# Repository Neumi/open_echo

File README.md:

---
layout: home
title: Open Echo
nav_exclude: true
---

<div align="center">
  
</div>

## Universal Open-Source SONAR Controller and Development Stack

An ongoing open-source hardware and software project for building sonar systems for testing, boating, bathymetry, and research.

[Discord](https://discord.com/invite/rerCyqAcrw) | [Getting Started Guide](documentation/getting_started/index.md) | [Hardware Files](https://github.com/neumi/open_echo/tree/main/TUSS4470_shield_002/TUSS4470_shield_hardware/TUSS4470_shield)

## Overview

Open Echo makes SONAR technology accessible for developers, researchers, and hobbyists. It supports a wide variety of commercial and DIY ultrasonic transducers in both water and air, covering frequencies from 40 kHz up to 1000 kHz.

Use cases range from reverse-engineering car parking sensors and reading depth data on a yacht, to operating a Lowrance Tripleshot side-scan transducer or streaming data to a Pixhawk on a custom boat.

### Key Features

* **Universal Transducer Support:** Works with commercial and DIY transducers in water and air.
* **Flexible Firmware:** Run the [RAW Data Firmware](documentation/getting_started/TUSS4470_firmware.md) to process echoes yourself, or the [NMEA Output Firmware](https://github.com/neumi/open_echo/tree/main/TUSS4470_shield_002/arduino/NMEA_DBT_OUT/NMEA_DBT_OUT.ino) for NMEA0183 DBT compatibility (sends depth data directly to PCs, Pixhawk, or marine controllers).
* **Python Interface:** The [desktop software](documentation/getting_started/desktop_interface.md) provides live raw data visualization and TCP data streaming.
* **Tested Range:** Confirmed depth tracking of >50 m in water.
* **Network Ready:** Includes a PicoW implementation (software only, the shield itself is Arduino UNO R3 compatible) that transfers RAW data over UDP directly to the Python interface.

## Hardware & Getting Started

The primary development platform is the [TUSS4470 Arduino Shield](documentation/getting_started/TUSS4470_hardware.md). It stacks directly on top of an Arduino Uno to drive the TUSS4470 ultrasonic driver.

**Upcoming Board:** A new development version is in the works and will hopefully be released in the coming weeks. It features an on-board boost converter and slightly improved signal routing.

* **Powering (Current Board):** Provide driver voltage via Arduino VIN or the external XT30 connector. You can also currently use an MT3608 boost converter to step up USB power to your required drive voltage (requires manual soldering until the new board is released).
* **Capabilities:** Drives transducers from 40–1000 kHz, filters signals, and sends raw echo data to the backend. It captures 1800 samples at 13.2 µs/sample (roughly an 18m range in water at 8-bit resolution). You can manually add delays in the code to extend the detection range for further distances.

### Getting the Hardware

1. **Elecrow (Pre-Built):** Buy a fully assembled and tested board here: [Elecrow Open Echo TUSS4470](https://www.elecrow.com/open-echo-tuss4470-development-shield.html)
2. **Build Your Own:** Order the [Hardware Files](https://github.com/neumi/open_echo/tree/main/TUSS4470_shield_002/TUSS4470_shield_hardware/TUSS4470_shield) from your preferred PCB manufacturer (JLCPCB recommended).
3. **Directly from me (Germany/EU):** If Elecrow is out of stock or you want to reduce shipping costs within Germany, email me at: `openechoes@gmail.com`.

> **Note:** All profits go directly toward supporting the project. Please understand that I can only provide support if you order the boards directly from me or Elecrow.

## Open Echo Interface Software

The [Python Interface Software](documentation/getting_started/desktop_interface.md) connects to boards running the RAW Data Firmware. It serves as a simple backend to view live echograms and output TCP depth data streams. (Configuration tweaking directly from the UI will be added later).

Live echogram in water (6x speed):  

*(Static raw data waterfall chart available [here](documentation/images/echo_software_screenshot.jpg))*

## Test Results: Baltic Sea

Tested using a built-in 150 kHz SEAFARER transducer, powered at 15-20 V via an MT3608 boost converter from USB. Data capture in the plots begins at the bottom.

<table>
  <tr>
    <td align="center">
      <br/>
      <sub><b>38 m range test</b></sub>
    </td>
    <td align="center">
      <br/>
      <sub><b>Kiel Channel sand and mud</b></sub>
    </td>
    <td align="center">
      <br/>
      <sub><b>Slope near Stollergrund</b></sub>
    </td>
  </tr>
  <tr>
    <td align="center">
      <br/>
      <sub><b>Stones and sandy seabed</b></sub>
    </td>
    <td align="center">
      <br/>
      <sub><b>Fish detection</b></sub>
    </td>
    <td align="center">
      <br/>
      <sub><b>Multiple reflections and seaweed</b></sub>
    </td>
  </tr>
</table>

## Transducers

Open Echo has been tested with multiple transducers. Here is a curated list of tested hardware:

| Transducer Name | Rating | Description | Freq. | Range Air/Water | Price | Link |
| --- | --- | --- | --- | --- | --- | --- |
| NASA / Seafarer 150kHz | ⭐⭐⭐ | NASA in-hull boat transducer for echo sounding / fish-finding | 150kHz | >2m / >50m | 50-100€ | [Link](https://www.nasamarine.com/product/depth-transducer-with-7-metre-cable/7) |
| Raymarine CPT-S | ⭐⭐⭐ | High-quality in-hull transducer with two frequencies | 50/200kHz | 2m / >50m | 200€ | [Link](https://www.raymarine.com/de-de/unsere-produkte/fischfinder-und-sonarmodule/fischfindergeber/cpt-s-durchbruchgeber) |
| Lowrance Tripleshot | ⭐⭐⭐ | Sidescan transducer (three FANS + temp + down-scan) | 200/455/600kHz | 0m / >20m | 200€ | [Link](https://www.echolotzentrum.de/shop/lowrance-tripleshot-heckgeber/) |
| Cheap Bathymetry | ⭐⭐⭐ | Good range and price/performance (can be hard to order) | 200kHz | 2m / >30m | 25€ | [Link](https://www.alibaba.com/product-detail/Range-customization-lakes-river-surveys-no_1600829423846.html) |
| Car Parking Sensor | ⭐⭐ | Great for air, works in water (not recommended for marine) | 40kHz | >7m / >30m | 5€ | [Link](https://de.aliexpress.com/item/1005006546490802.html) |
| Water Flow Sensor | ⭐⭐ | Cheap (Air & Water). Very narrow beam in water (~5°)! | 1000kHz | 0.25m / >10m | 16€ (5pcs) | [Link](https://de.aliexpress.com/item/32818381566.html) |
| Sinter Glass (Air Only) | ⭐ | Sinter glass matching layer, strictly for air use | 200kHz | 0.8m / (>8m) | 10€ | [Link](https://de.aliexpress.com/item/1005006007865920.html) |
| Encapsulated Transducers | ⭐ | Good for short-range testing at higher frequencies | 200-400kHz | ?m / ?m | 9-18€ | [Link](https://de.aliexpress.com/item/4000389134890.html) |
| Small PZT Only | ⭐ | Bare component, only for raw experimentation | 200kHz | 0.2m / ?m | 10€ | [Link](https://de.aliexpress.com/item/1005007032482539.html) |

> **Note:** The range values were measured using the TUSS4470 shield on an Arduino Uno with an MT3608 boost converter set to 20V for `vDRV`. Consider them approximate.

> **Tip:** Lower frequencies propagate farther, while higher frequencies produce narrower beams and more detailed echoes. For bathymetry, the first four options work best. Most commercial marine-grade transducers are suitable as long as they operate between 40 and 1000 kHz.

## Media & Resources

### Videos

https://www.youtube.com/watch?v=R3_NO2F7PsI  
https://www.youtube.com/watch?v=msbLVsY8xhQ  
https://www.youtube.com/watch?v=eJ8jVEQSx_Y  
https://www.youtube.com/watch?v=Bxh3rWd5RZk  
https://www.youtube.com/watch?v=UDYWQIizN7A  

### Links

* [Rapp Instruments: Side-Scan Sonar Info](https://www.rapp-instruments.de/RemoteSensing/Roves/sidescan/sidescan.htm)
* [Related Sonar Explanation Video](https://www.youtube.com/watch?v=ZtUkt8Q4EJE)

## Acknowledgments & Support

A big thanks to **[www.kogger.tech](http://www.kogger.tech)** for their continued support!

Thanks to our contributors:
* Check out the [Cheap Yellow Display Implementation](https://github.com/matztam/open_echo_cyd_display) by @matztam.
* Thanks to [@JohnCHarrington](https://github.com/JohnCHarrington/open_echo) for the firmware and software contributions.

### Star History

## Citation

If you use `open_echo` in your work or research, please cite the project:

* **ORCID:**  [0009-0003-9829-8959](https://orcid.org/0009-0003-9829-8959)

**BibTeX:**

```bibtex
@misc{open_echo,
  author       = {Jan Neumann},
  title        = {open\_echo},
  year         = {2026},
  publisher    = {GitHub},
  journal      = {GitHub Repository},
  howpublished = {\url{[https://github.com/Neumi/open_echo](https://github.com/Neumi/open_echo)}},
  note         = {ORCID: [https://orcid.org/0009-0003-9829-8959](https://orcid.org/0009-0003-9829-8959)}
}

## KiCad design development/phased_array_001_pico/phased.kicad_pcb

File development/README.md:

# open_echo development
Less tested code, PCB designs and files. Not documented or ready for external use.

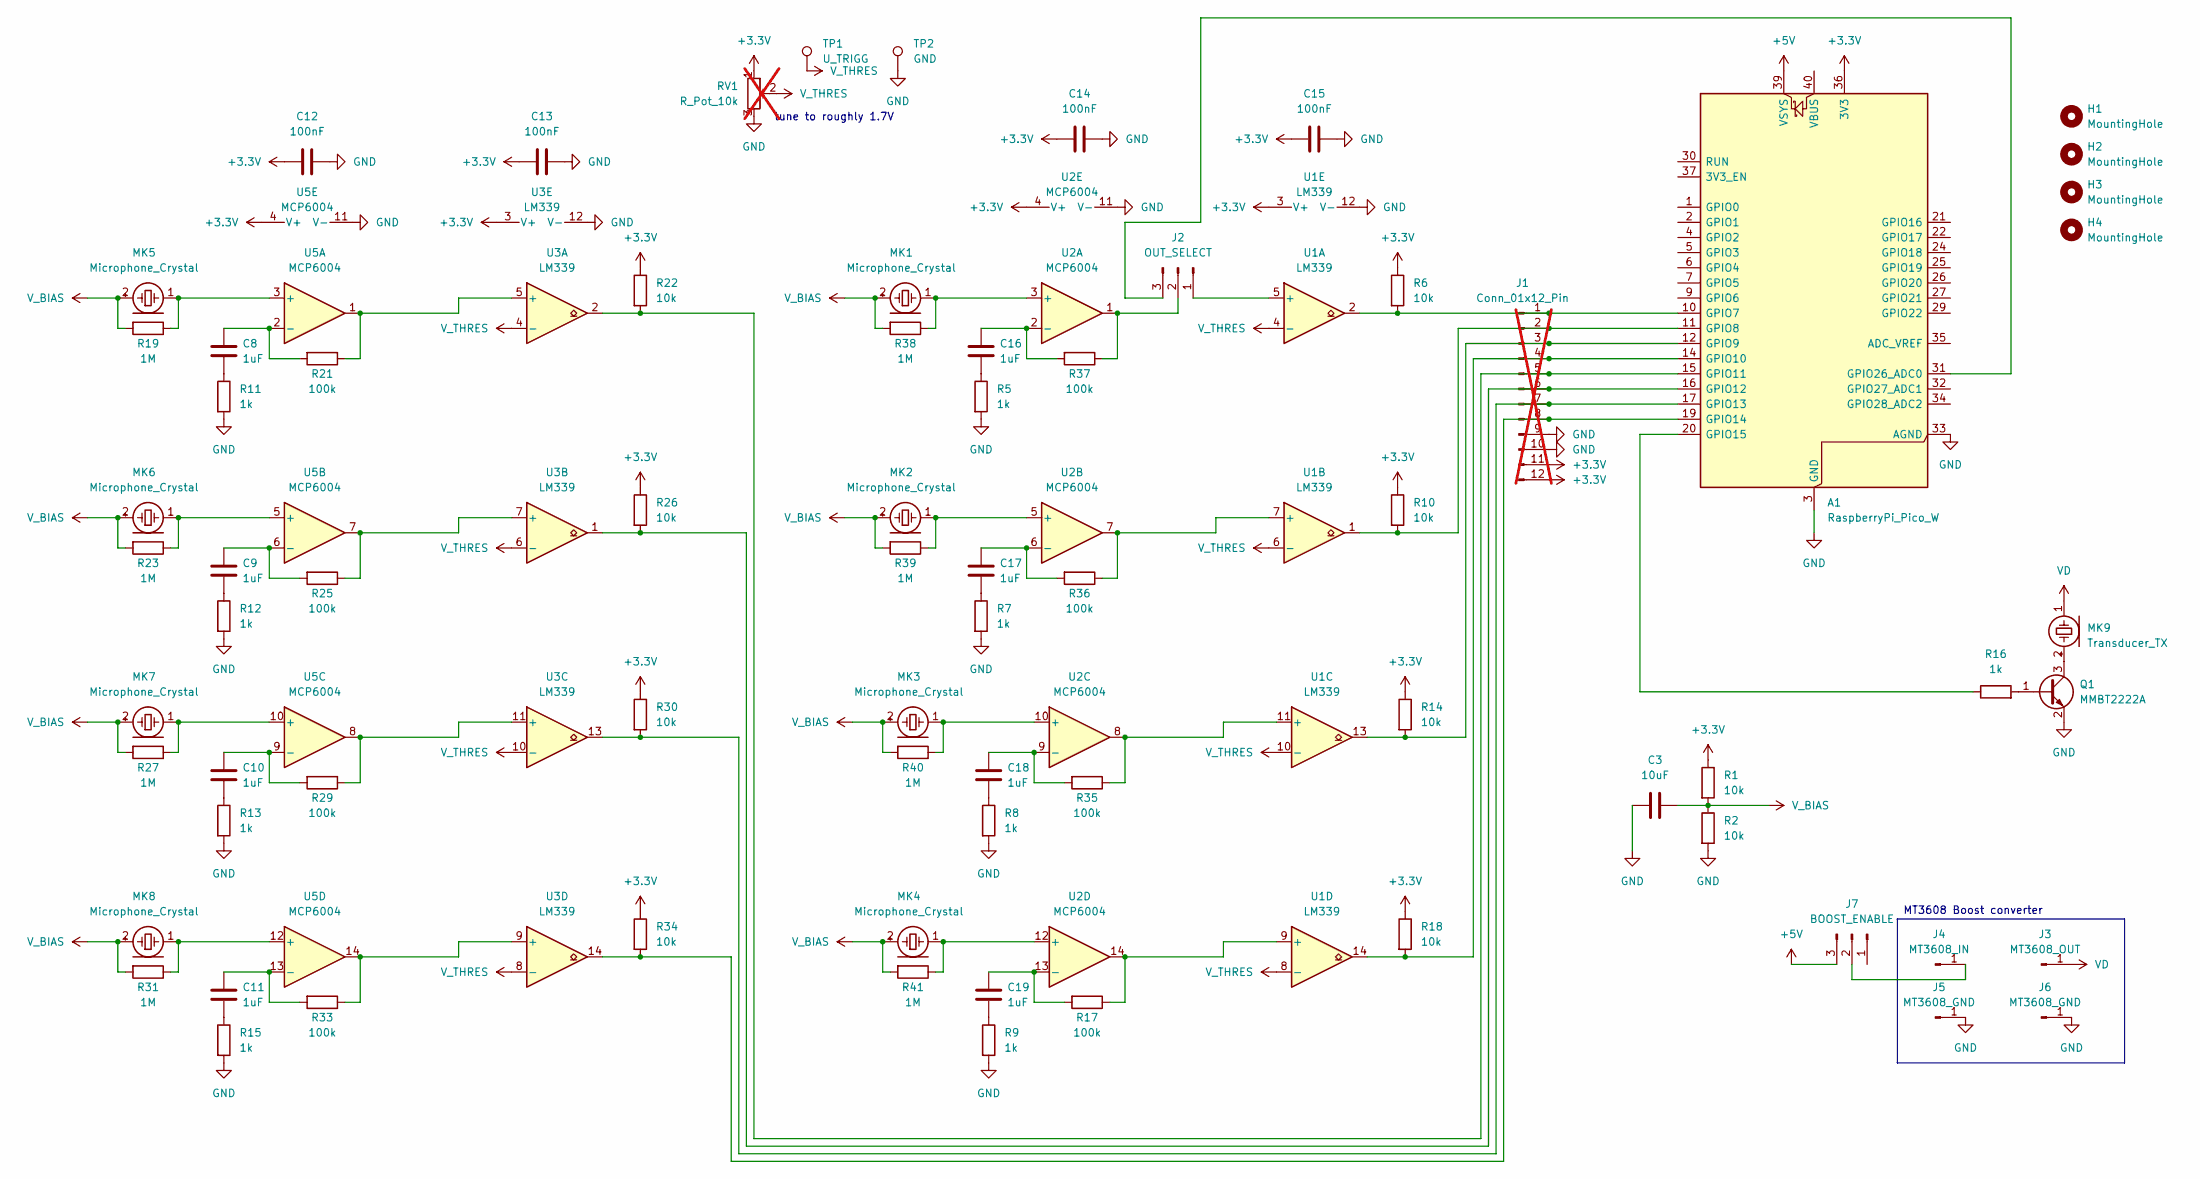
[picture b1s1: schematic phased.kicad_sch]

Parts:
A1: RaspberryPi_Pico_W; RaspberryPi_Pico_Common_Unspecified
C3: 10uF; C_0603_1608Metric; LCSC C19702
C8, C9, C10, C11, C16, C17, C18, C19: 1uF; C_0603_1608Metric; LCSC C15849
C12, C13, C14, C15: 100nF; C_0603_1608Metric; LCSC C1525
H1, H2, H3, H4: MountingHole; MountingHole_3.2mm_M3
J1: Conn_01x12_Pin; PinHeader_1x12_P2.54mm_Vertical; not fitted
J2: OUT_SELECT; PinHeader_1x03_P2.54mm_Vertical
J3: MT3608_OUT; PinHeader_1x01_P2.54mm_Vertical
J4: MT3608_IN; PinHeader_1x01_P2.54mm_Vertical
J5, J6: MT3608_GND; PinHeader_1x01_P2.54mm_Vertical
J7: BOOST_ENABLE; PinHeader_1x03_P2.54mm_Vertical
MK1, MK2, MK3, MK4, MK5, MK6, MK7, MK8: Microphone_Crystal; JST_EH_S2B-EH_1x02_P2.50mm_Horizontal
MK9: Transducer_TX; JST_EH_S2B-EH_1x02_P2.50mm_Horizontal
Q1: MMBT2222A; SOT-23; LCSC C8512
R1, R2, R6, R10, R14, R18, R22, R26, R30, R34: 10k; R_0603_1608Metric; LCSC C25804
R5, R7, R8, R9, R11, R12, R13, R15, R16: 1k; R_0603_1608Metric; LCSC C21190
R17, R21, R25, R29, R33, R35, R36, R37: 100k; R_0603_1608Metric; LCSC C25803
R19, R23, R27, R31, R38, R39, R40, R41: 1M; R_0603_1608Metric; LCSC C22935
RV1: R_Pot_10k; Potentiometer_Bourns_3296W_Vertical; not fitted
TP1: U_TRIGG; TestPoint_Loop_D2.54mm_Drill1.5mm_Beaded
TP2: GND; TestPoint_Loop_D2.54mm_Drill1.5mm_Beaded
U1, U3: LM339; SOIC-14_3.9x8.7mm_P1.27mm; LCSC C7948
U2, U5: MCP6004; SOIC-14_3.9x8.7mm_P1.27mm; LCSC C7378

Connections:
+3.3V: A1.36 (3V3), C12.1, C13.1, C14.1, C15.1, J1.11, J1.12, R1.1, R6.1, R10.1, R14.1, R18.1, R22.1, R26.1, R30.1, R34.1, RV1.1, U1.3 (V+), U2.4 (V+), U3.3 (V+), U5.4 (V+)
+5V: A1.39 (VSYS), J7.3
GND: A1.3 (GND), A1.8 (GND), A1.13 (GND), A1.18 (GND), A1.23 (GND), A1.28 (GND), A1.33 (AGND), A1.38 (GND), C3.2, C12.2, C13.2, C14.2, C15.2, J1.9, J1.10, J5.1 (Pin_1_1), J6.1 (Pin_1_1), Q1.2 (E), R2.2, R5.2, R7.2, R8.2, R9.2, R11.2, R12.2, R13.2, R15.2, RV1.3, TP2.1 (1_1), U1.12 (V-), U2.11 (V-), U3.12 (V-), U5.11 (V-)
unnamed: A1.10 (GPIO7), J1.1, R6.2, U1.2
unnamed: A1.11 (GPIO8), J1.2, R10.2, U1.1
unnamed: A1.12 (GPIO9), J1.3, R14.2, U1.13
unnamed: A1.14 (GPIO10), J1.4, R18.2, U1.14
unnamed: A1.15 (GPIO11), J1.5, R22.2, U3.2
unnamed: A1.16 (GPIO12), J1.6, R26.2, U3.1
unnamed: A1.17 (GPIO13), J1.7, R30.2, U3.13
unnamed: A1.19 (GPIO14), J1.8, R34.2, U3.14
unnamed: A1.20 (GPIO15), R16.1
unnamed: A1.31 (GPIO26_ADC0), J2.3
unnamed: C8.1, R11.1
unnamed: C9.1, R12.1
unnamed: C10.1, R13.1
unnamed: C11.1, R15.1
unnamed: C16.1, R5.1
unnamed: C17.1, R7.1
unnamed: C18.1, R8.1
unnamed: C19.1, R9.1
unnamed: J2.1, U1.5 (+)
unnamed: J2.2, R37.1, U2.1
unnamed: J4.1 (Pin_1_1), J7.2
unnamed: MK1.1 (-), R38.1, U2.3 (+)
unnamed: MK2.1 (-), R39.1, U2.5 (+)
unnamed: MK3.1 (-), R40.1, U2.10 (+)
unnamed: MK4.1 (-), R41.1, U2.12 (+)
unnamed: MK5.1 (-), R19.1, U5.3 (+)
unnamed: MK6.1 (-), R23.1, U5.5 (+)
unnamed: MK7.1 (-), R27.1, U5.10 (+)
unnamed: MK8.1 (-), R31.1, U5.12 (+)
unnamed: MK9.2 (+), Q1.3 (C)
unnamed: Q1.1 (B), R16.2
unnamed: R36.1, U1.7 (+), U2.7
unnamed: R35.1, U1.11 (+), U2.8
unnamed: R17.1, U1.9 (+), U2.14
unnamed: C16.2, R37.2, U2.2 (-)
unnamed: C17.2, R36.2, U2.6 (-)
unnamed: C18.2, R35.2, U2.9 (-)
unnamed: C19.2, R17.2, U2.13 (-)
unnamed: R21.1, U3.5 (+), U5.1
unnamed: R25.1, U3.7 (+), U5.7
unnamed: R29.1, U3.11 (+), U5.8
unnamed: R33.1, U3.9 (+), U5.14
unnamed: C8.2, R21.2, U5.2 (-)
unnamed: C9.2, R25.2, U5.6 (-)
unnamed: C10.2, R29.2, U5.9 (-)
unnamed: C11.2, R33.2, U5.13 (-)
VD: J3.1 (Pin_1_1), MK9.1 (-)
V_BIAS: C3.1, MK1.2 (+), MK2.2 (+), MK3.2 (+), MK4.2 (+), MK5.2 (+), MK6.2 (+), MK7.2 (+), MK8.2 (+), R1.2, R2.1, R19.2, R23.2, R27.2, R31.2, R38.2, R39.2, R40.2, R41.2
V_THRES: RV1.2, TP1.1 (1_1), U1.4 (-), U1.6 (-), U1.8 (-), U1.10 (-), U3.4 (-), U3.6 (-), U3.8 (-), U3.10 (-)

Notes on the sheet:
tune to roughly 1.7V
MT3608 Boost converter

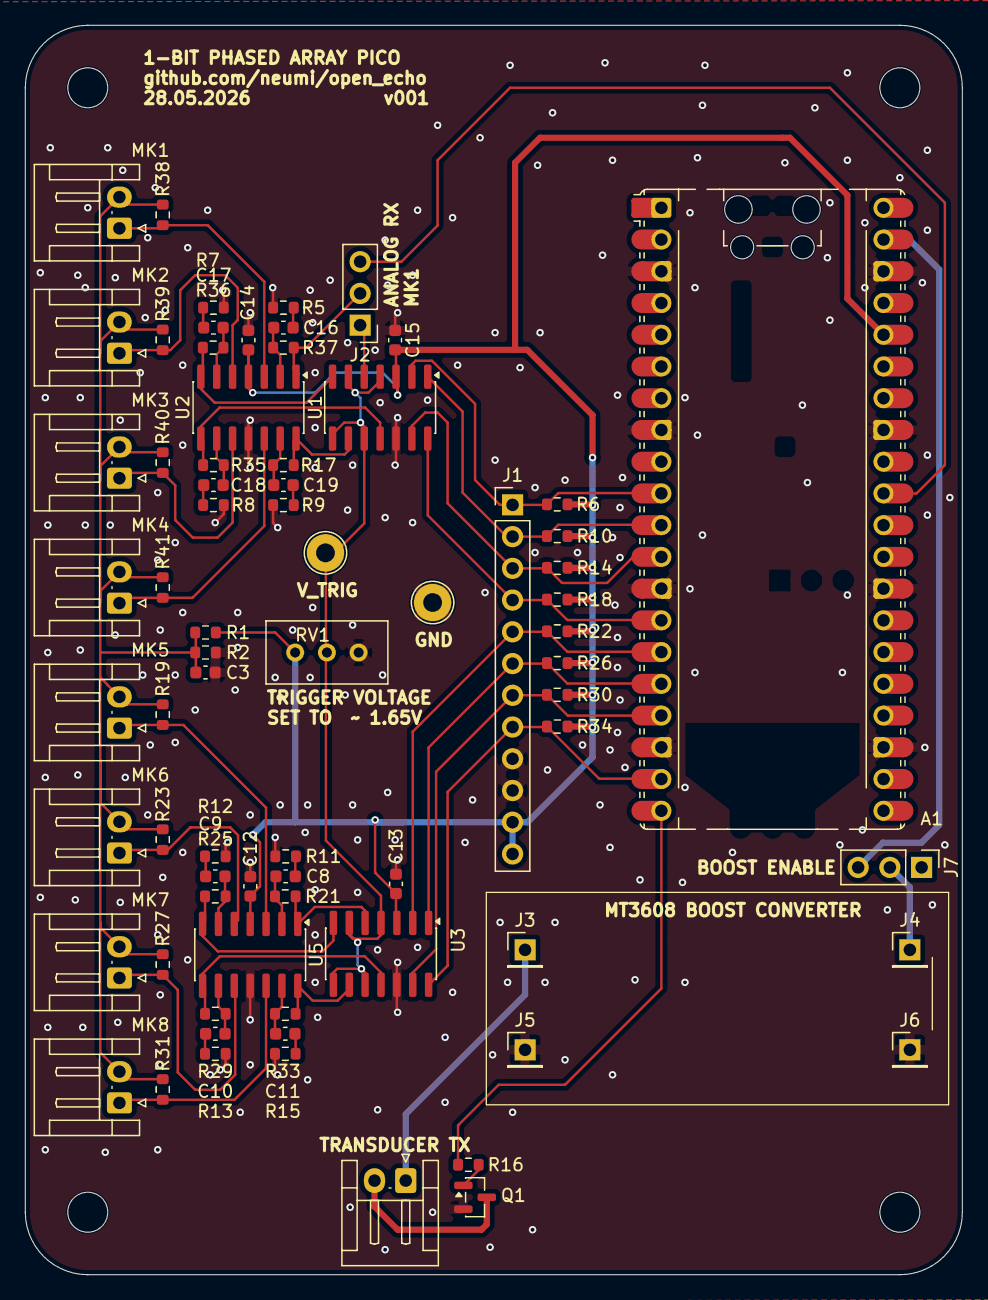
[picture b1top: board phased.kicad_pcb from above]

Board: 2 copper layers, 75.0 x 100.0 mm, 77 parts (0 on the bottom side), 52 nets.

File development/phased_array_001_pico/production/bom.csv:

Designator,Footprint,Quantity,Value,LCSC Part #
A1,RaspberryPi_Pico_Common_Unspecified,1,RaspberryPi_Pico_W,
"C10, C11, C16, C17, C18, C19, C8, C9",0603,8,1uF,C15849
"C12, C13, C14, C15",0603,4,100nF,C1525
C3,0603,1,10uF,C19702
J2,PinHeader_1x03_P2.54mm_Vertical,1,OUT_SELECT,
J3,PinHeader_1x01_P2.54mm_Vertical,1,MT3608_OUT,
J4,PinHeader_1x01_P2.54mm_Vertical,1,MT3608_IN,
"J5, J6",PinHeader_1x01_P2.54mm_Vertical,2,MT3608_GND,
J7,PinHeader_1x03_P2.54mm_Vertical,1,BOOST_ENABLE,
"MK1, MK2, MK3, MK4, MK5, MK6, MK7, MK8",JST_EH_S2B-EH_1x02_P2.50mm_Horizontal,8,Microphone_Crystal,
MK9,JST_EH_S2B-EH_1x02_P2.50mm_Horizontal,1,Transducer_TX,
Q1,SOT-23,1,MMBT2222A,C8512
"R1, R10, R14, R18, R2, R22, R26, R30, R34, R6",0603,10,10k,C25804
"R11, R12, R13, R15, R16, R5, R7, R8, R9",0603,9,1k,C21190
"R17, R21, R25, R29, R33, R35, R36, R37",0603,8,100k,C25803
"R19, R23, R27, R31, R38, R39, R40, R41",0603,8,1M,C22935
TP1,TestPoint_Loop_D2.54mm_Drill1.5mm_Beaded,1,U_TRIGG,
TP2,TestPoint_Loop_D2.54mm_Drill1.5mm_Beaded,1,GND,
"U1, U3",SOIC-14_3.9x8.7mm_P1.27mm,2,LM339,C7948
"U2, U5",SOIC-14_3.9x8.7mm_P1.27mm,2,MCP6004,C7378

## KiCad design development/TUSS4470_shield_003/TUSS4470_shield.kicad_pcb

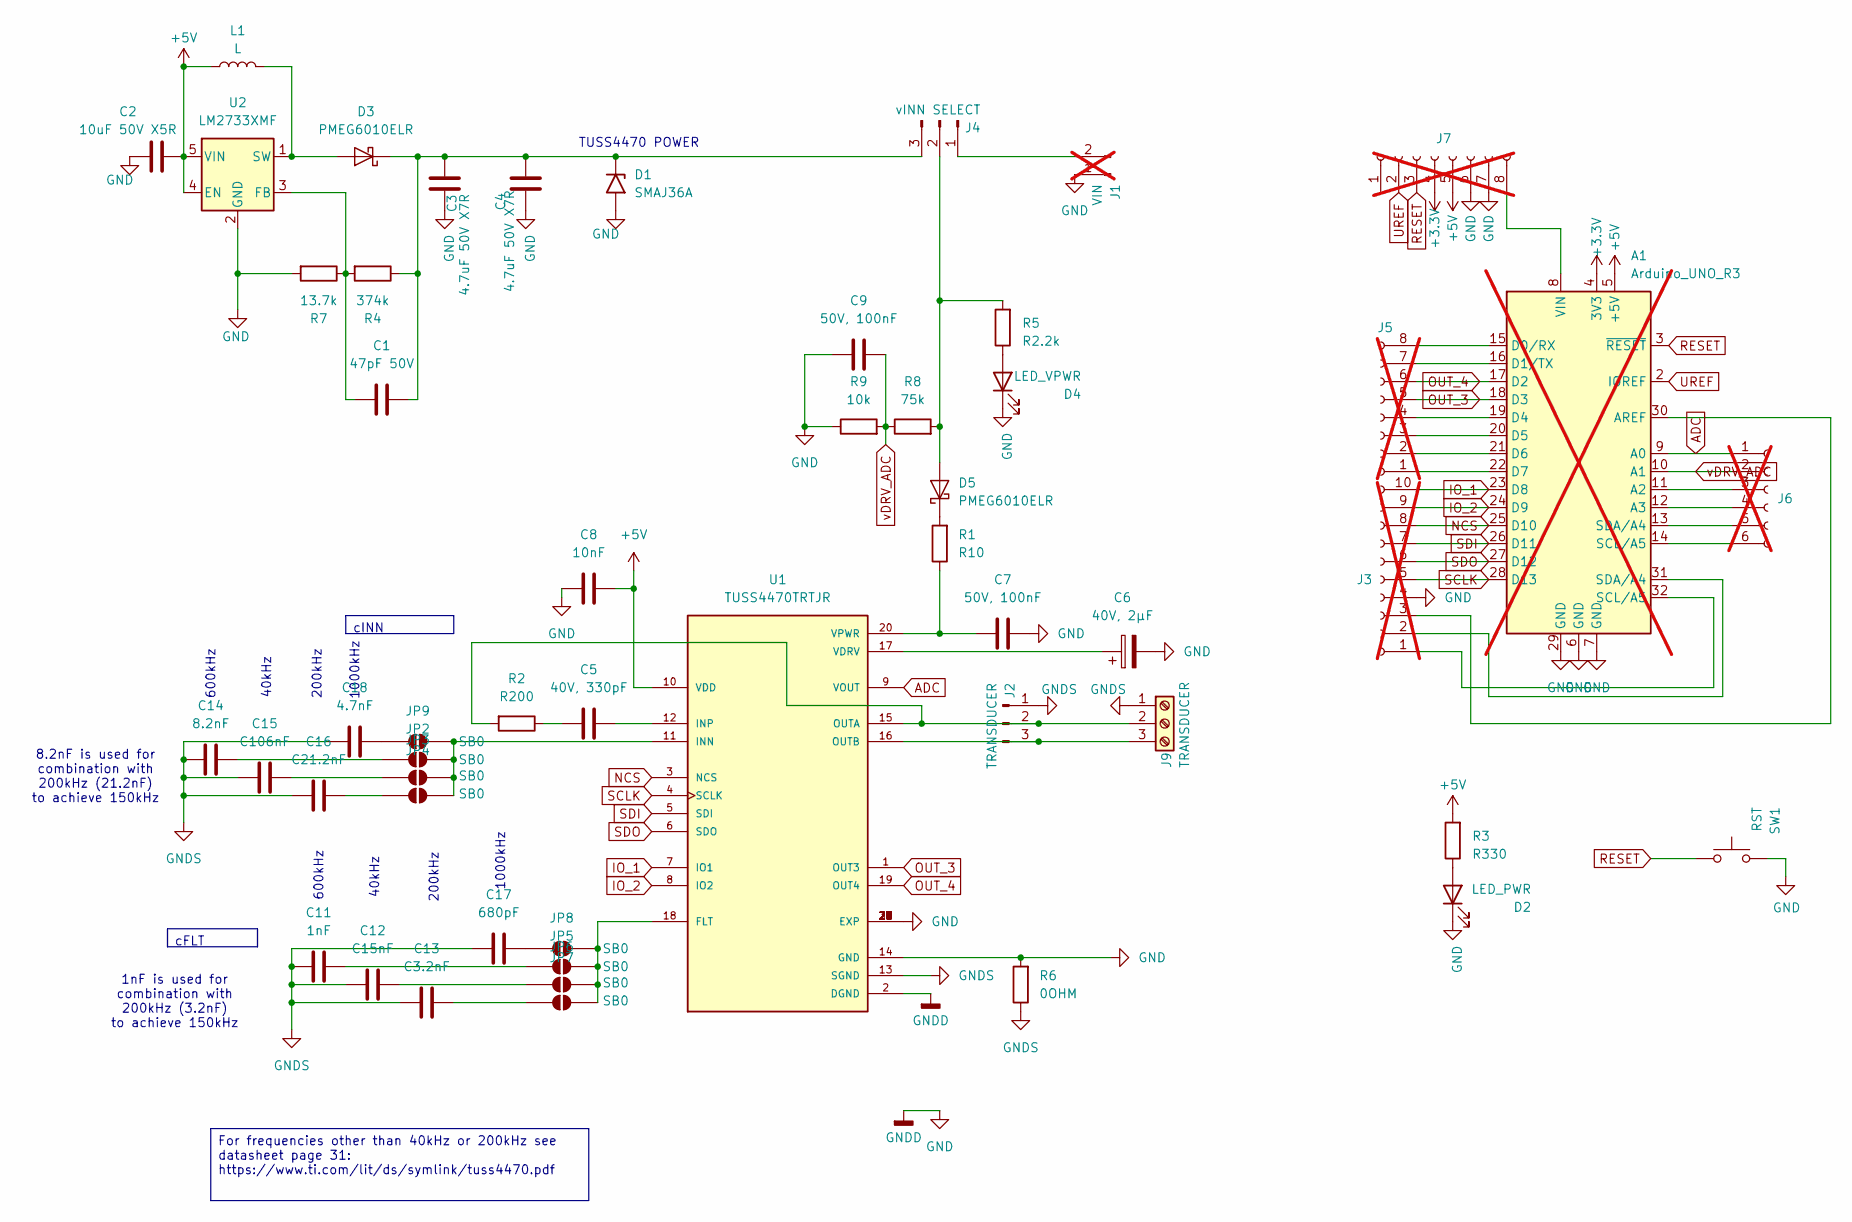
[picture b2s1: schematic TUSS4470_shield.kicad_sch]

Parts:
A1: Arduino_UNO_R3; not fitted
C1: 47pF 50V; R_0603_1608Metric; LCSC C1671
C2: 10uF 50V X5R; C_1206_3216Metric; LCSC C13585
C3, C4: 4.7uF 50V X7R; C_1206_3216Metric; LCSC C29823
C5: 40V, 330pF; C_0603_1608Metric; LCSC C1664
C6: 40V, 2µF; C_1206_3216Metric; LCSC C50254
C7, C9: 50V, 100nF; C_0603_1608Metric; LCSC C14663
C8: 10nF; C_0603_1608Metric; LCSC C57112
C11: 1nF; C_0603_1608Metric; LCSC C1588
C12: C15nF; C_0603_1608Metric; LCSC C1596
C13: C3.2nF; C_0603_1608Metric; LCSC C1613
C14: 8.2nF; C_0603_1608Metric; LCSC C1322360
C15: C106nF; C_0603_1608Metric; LCSC C14663
C16: C21.2nF; C_0603_1608Metric; LCSC C21122
C17: 680pF; C_0603_1608Metric; LCSC C1630
C18: 4.7nF; C_0603_1608Metric; LCSC C53987
D1: SMAJ36A; D_SMA; LCSC C19077550
D2: LED_PWR; LED_0805_2012Metric; LCSC C84256
D3, D5: PMEG6010ELR; Nexperia_CFP3_SOD-123W; LCSC C179432
D4: LED_VPWR; LED_0805_2012Metric; LCSC C84256
J1: VIN; AMASS_XT30PW-M_1x02_P2.50mm_Horizontal; LCSC C431092; not fitted
J2: TRANSDUCER; PinHeader_1x03_P2.54mm_Vertical
J3: Conn_01x10_Socket; PinHeader_1x10_P2.54mm_Vertical; not fitted
J4: vINN SELECT; PinHeader_1x03_P2.54mm_Vertical; LCSC C49257
J5, J7: Conn_01x08_Socket; PinHeader_1x08_P2.54mm_Vertical; not fitted
J6: Conn_01x06_Socket; PinHeader_1x06_P2.54mm_Vertical; not fitted
J9: TRANSDUCER; TerminalBlock_4Ucon_1x03_P3.50mm_Horizontal
JP2, JP3, JP4, JP5, JP6, JP7, JP8, JP9: SB0; SolderJumper-2_P1.3mm_Open_RoundedPad1.0x1.5mm
L1: L; L_Taiyo-Yuden_NR-60xx; LCSC C16218
R1: R10; R_1206_3216Metric; LCSC C17903
R2: R200; R_1206_3216Metric; LCSC C25361
R3: R330; R_0603_1608Metric; LCSC C23138
R4: 374k; R_0603_1608Metric; LCSC C25815
R5: R2.2k; R_0603_1608Metric; LCSC C4190
R6: 0OHM; R_0805_2012Metric; LCSC C17477
R7: 13.7k; R_0603_1608Metric; LCSC C325658
R8: 75k; R_0603_1608Metric; LCSC C23242
R9: 10k; R_0603_1608Metric; LCSC C25804
SW1: RST; SW_Push_1P1T_NO_CK_KSC7xxJ; LCSC C318884
U1: TUSS4470TRTJR; QFN-20-1EP_4x4mm_P0.5mm_EP2.5x2.5mm_ThermalVias; PARTREV December 2019; LCSC C1855776
U2: LM2733XMF; SOT-23-5

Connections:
+3.3V: A1.4 (3V3), J7.4
+5V: A1.5 (+5V), C2.2, C8.2, J7.5, L1.1, R3.2, U1.10 (VDD), U2.4 (EN), U2.5 (VIN)
ADC: A1.9 (A0), J6.1, U1.9 (VOUT)
GND: A1.6 (GND), A1.7 (GND), A1.29 (GND), C2.1, C3.1, C4.1, C6.2, C7.2, C8.1, C9.1, D1.2 (A2), D2.1 (K), D4.1 (K), J1.1, J3.4, J7.6, J7.7, R6.2, R7.2, R9.1, SW1.2, U1.2 (DGND), U1.14 (GND), U1.21 (EXP), U1.22 (EXP), U1.23 (EXP), U1.24 (EXP), U1.25 (EXP), U1.26 (EXP), U1.27 (EXP), U1.28 (EXP), U1.29 (EXP), U1.30 (EXP), U2.2 (GND)
GNDS: C11.1, C12.1, C13.1, C14.1, C15.1, C16.1, C17.1, C18.1, J2.1, J9.1, R6.1, U1.13 (SGND)
IO_1: A1.23 (D8), J3.10, U1.7 (IO1)
IO_2: A1.24 (D9), J3.9, U1.8 (IO2)
NCS: A1.25 (D10), J3.8, U1.3 (NCS)
unnamed: A1.11 (A2), J6.3
unnamed: A1.12 (A3), J6.4
unnamed: A1.30 (AREF), J3.3
unnamed: A1.15 (D0/RX), J5.8
unnamed: A1.16 (D1/TX), J5.7
unnamed: A1.19 (D4), J5.4
unnamed: A1.20 (D5), J5.3
unnamed: A1.21 (D6), J5.2
unnamed: A1.22 (D7), J5.1
unnamed: A1.8 (VIN), J7.8
unnamed: C5.1, R2.1
unnamed: C1.2, C3.2, C4.2, D1.1 (A1), D3.1 (K), J4.3, R4.1
unnamed: D2.2 (A), R3.1
unnamed: D3.2 (A), L1.2, U2.1 (SW)
unnamed: D4.2 (A), R5.1
unnamed: D5.2 (A), J4.2, R5.2, R8.2
unnamed: D5.1 (K), R1.2
unnamed: J1.2, J4.1
unnamed: J2.2, J9.2, R2.2, U1.15 (OUTA)
unnamed: J2.3, J9.3, U1.16 (OUTB)
unnamed: A1.32 (SCL/A5), J3.1
unnamed: A1.31 (SDA/A4), J3.2
unnamed: A1.13 (SDA/A4), J6.5
unnamed: A1.14 (SCL/A5), J6.6
unnamed: C14.2, JP2.1 (A)
unnamed: JP2.2 (B), JP3.2 (B), JP4.2 (B), JP9.2 (B), U1.11 (INN)
unnamed: C15.2, JP3.1 (A)
unnamed: C16.2, JP4.1 (A)
unnamed: C11.2, JP5.1 (A)
unnamed: JP5.2 (B), JP6.2 (B), JP7.2 (B), JP8.2 (B), U1.18 (FLT)
unnamed: C12.2, JP6.1 (A)
unnamed: C13.2, JP7.1 (A)
unnamed: C17.2, JP8.1 (A)
unnamed: C18.2, JP9.1 (A)
unnamed: C5.2, U1.12 (INP)
unnamed: C6.1, U1.17 (VDRV)
unnamed: C7.1, R1.1, U1.20 (VPWR)
unnamed: C1.1, R4.2, R7.1, U2.3 (FB)
OUT_3: A1.18 (D3), J5.5, U1.1 (OUT3)
OUT_4: A1.17 (D2), J5.6, U1.19 (OUT4)
RESET: A1.3 (~RESET), J7.3, SW1.1
SCLK: A1.28 (D13), J3.5, U1.4 (SCLK)
SDI: A1.26 (D11), J3.7, U1.5 (SDI)
SDO: A1.27 (D12), J3.6, U1.6 (SDO)
UREF: A1.2 (IOREF), J7.2
vDRV_ADC: A1.10 (A1), C9.2, J6.2, R8.1, R9.2

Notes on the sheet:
200kHz
40kHz
8.2nF is used for combination with 200kHz (21.2nF) to achieve 150kHz
600kHz
1nF is used for combination with 200kHz (3.2nF) to achieve 150kHz
1000kHz
TUSS4470 POWER
cFLT
For frequencies other than 40kHz or 200kHz see datasheet page 31: https://www.ti.com/lit/ds/symlink/tuss4470.pdf
cINN

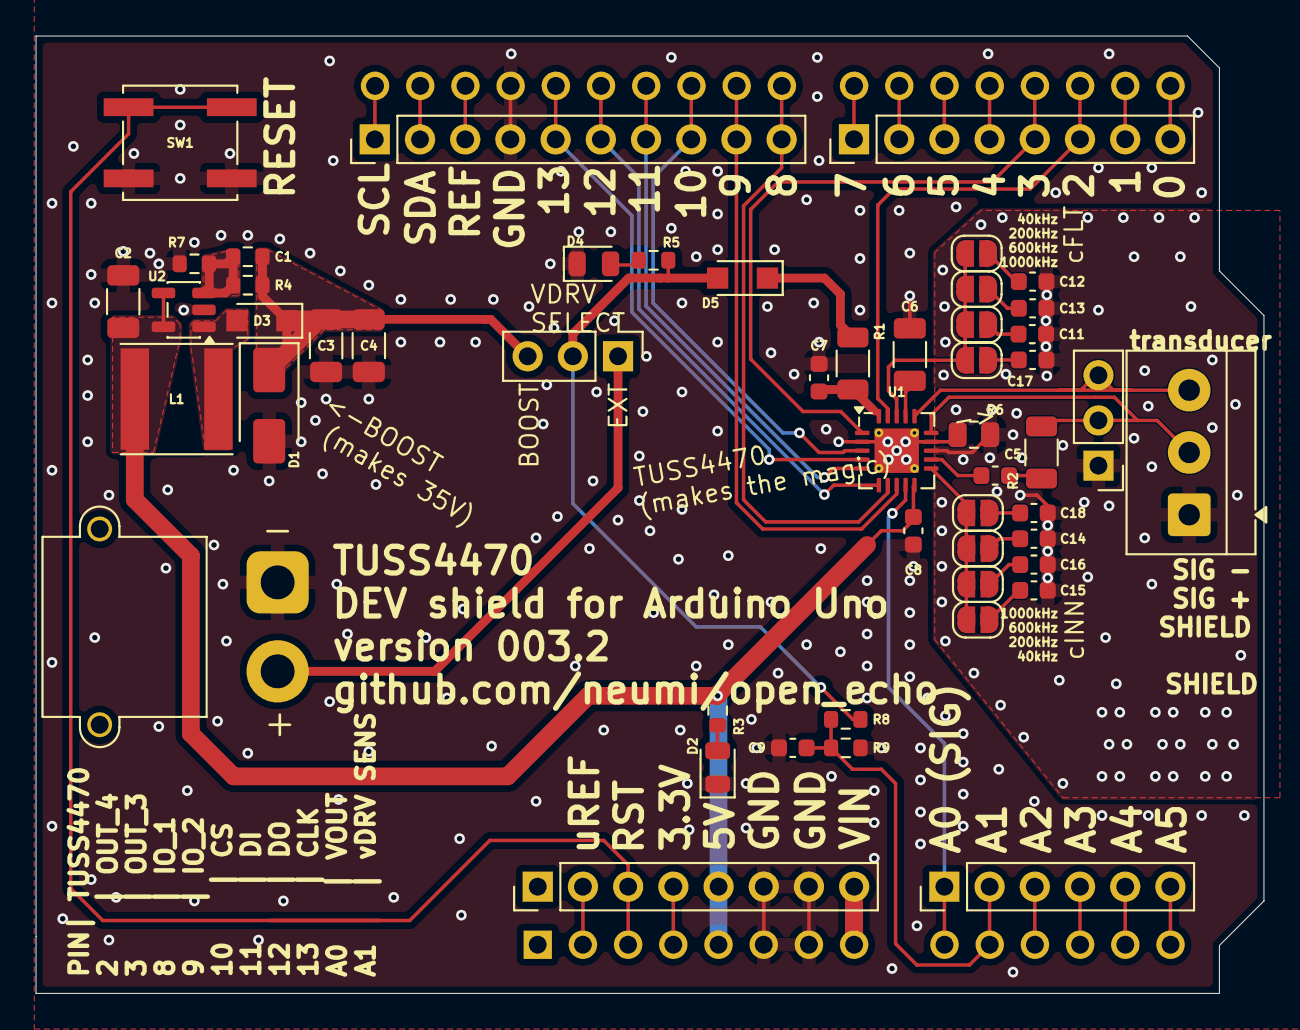
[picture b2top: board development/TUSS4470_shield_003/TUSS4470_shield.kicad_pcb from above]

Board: 2 copper layers, 69.0 x 53.8 mm, 52 parts (1 on the bottom side), 54 nets.

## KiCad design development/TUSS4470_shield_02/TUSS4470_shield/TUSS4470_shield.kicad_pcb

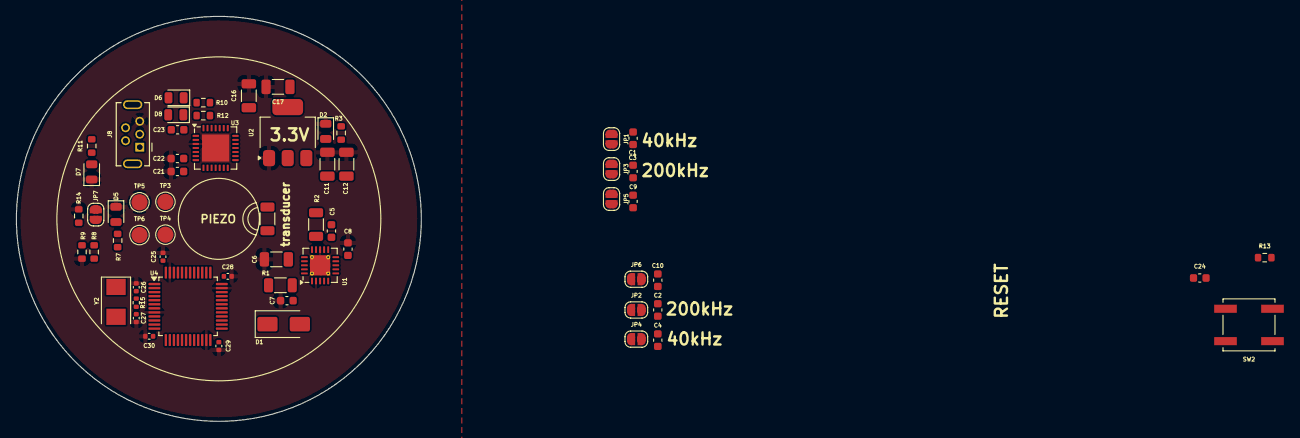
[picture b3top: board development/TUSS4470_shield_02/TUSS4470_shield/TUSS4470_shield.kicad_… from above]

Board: 2 copper layers, 50.0 x 50.0 mm, 61 parts (0 on the bottom side), 36 nets, no tracks yet.

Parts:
C1: C15nF; C_0603_1608Metric
C2: C106nF; C_0603_1608Metric
C3: C3.2nF; C_0603_1608Metric
C4: C21.2nF; C_0603_1608Metric
C5: 40V, 330pF; C_0603_1608Metric
C6: 40V, 2µF; C_1206_3216Metric
C7: 50V, 100nF; C_0603_1608Metric
C8: 10nF; C_0603_1608Metric
C9, C10: CXXnF; C_0603_1608Metric
C11, C16: C100nF; C_1206_3216Metric
C12, C17: C47uF; C_1206_3216Metric
C21, C22, C23, C24: C100nF; C_0603_1608Metric
C25, C28, C29, C30: C100nF; C_0402_1005Metric
C26, C27: C22pF; C_0402_1005Metric
D1: 1N4001; D_SMA
D2: LED_PWR; LED_0805_2012Metric
D5: LED_PC13; LED_0805_2012Metric
D6: TX; LED_0805_2012Metric
D7: LED_3.3V_PWR; LED_0805_2012Metric
D8: RX; LED_0805_2012Metric
J8: USB_B_Mini; USB_Mini-B_Tensility_54-00023_Vertical
JP1, JP2: 40kHz; SolderJumper-2_P1.3mm_Open_RoundedPad1.0x1.5mm
JP3, JP4: 200kHz; SolderJumper-2_P1.3mm_Open_RoundedPad1.0x1.5mm
JP5, JP6: CUSTOM kHz; SolderJumper-2_P1.3mm_Open_RoundedPad1.0x1.5mm
JP7: termination_jumper; SolderJumper-2_P1.3mm_Open_RoundedPad1.0x1.5mm
R1: R10; R_1206_3216Metric
R2: R200; R_1206_3216Metric
R3, R10, R11, R12: R330; R_0603_1608Metric
R7, R8, R9: R1k; R_0603_1608Metric
R13, R14: R10k; R_0603_1608Metric
R15: R1M; R_0402_1005Metric
SW2: RST; SW_Push_1P1T_NO_CK_KSC7xxJ
TP3: RX; TestPoint_Pad_D2.0mm
TP4: TX; TestPoint_Pad_D2.0mm
TP5: GND; TestPoint_Pad_D2.0mm
TP6: 3.3V; TestPoint_Pad_D2.0mm
U1: TUSS4470TRTJR; QFN-20-1EP_4x4mm_P0.5mm_EP2.5x2.5mm_ThermalVias
U2: AMS1117-3.3; SOT-223-3_TabPin2
U3: CP2102N-A01-GQFN28; QFN-28-1EP_5x5mm_P0.5mm_EP3.35x3.35mm
U4: STM32F103C8Tx; LQFP-48_7x7mm_P0.5mm
Y1: Crystal; R_1206_3216Metric
Y2: Crystal; Crystal_SMD_5032-2Pin_5.0x3.2mm

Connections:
5V_voltage_detect: R8.2, R9.1, U4.19 (PB1)
+3.3V: C16.1, C17.1, C25.1, C28.1, C29.1, C30.1, D6.2 (A), D8.2 (A), JP7.2 (B), R11.2, R13.1, TP6.1, U2.2 (VO), U4.9 (VDDA), U4.24 (VDD), U4.36 (VDD), U4.48 (VDD)
+5V: C8.2, C11.1, C12.1, R3.2, R8.1, U1.10 (VDD), U2.3 (VI)
BOOT_0: JP7.1 (A), R14.1, U4.44 (BOOT0)
GND: C1.2, C2.2, C3.2, C4.2, C6.2, C7.2, C8.1, C9.2, C10.2, C11.2, C12.2, C16.2, C17.2, C21.1, C22.1, C24.2, C25.2, C26.1, C27.2, C28.2, C29.2, C30.2, D2.1 (K), D5.1 (K), D7.1 (K), J8.5 (GND), R9.2, R14.2, SW2.2, TP5.1, U1.2 (DGND), U1.13 (SGND), U1.14 (GND), U1.21 (EXP), U2.1 (GND), U3.3 (GND), U3.29 (GND), U4.8 (VSSA), U4.23 (VSS), U4.35 (VSS), U4.47 (VSS)
unnamed: C5.1, R2.1
unnamed: D1.1 (K), R1.2
unnamed: D2.2 (A), R3.1
unnamed: D5.2 (A), R7.1
unnamed: D6.1 (K), R10.1
unnamed: D7.2 (A), R11.1
unnamed: D8.1 (K), R12.1
unnamed: J8.3 (D+), U3.4 (D+)
unnamed: J8.2 (D-), U3.5 (D-)
unnamed: C21.2, J8.1 (VBUS), U3.7 (REGIN), U3.8 (VBUS)
unnamed: C1.1, JP1.1 (A)
unnamed: JP1.2 (B), JP3.2 (B), JP5.2 (B), U1.18 (FLT)
unnamed: C2.1, JP2.1 (A)
unnamed: JP2.2 (B), JP4.2 (B), JP6.2 (B), U1.11 (INN)
unnamed: C3.1, JP3.1 (A)
unnamed: C4.1, JP4.1 (A)
unnamed: C9.1, JP5.1 (A)
unnamed: C10.1, JP6.1 (A)
unnamed: C5.2, U1.12 (INP)
unnamed: R2.2, U1.15 (OUTA), Y1.2
unnamed: U1.16 (OUTB), Y1.1
unnamed: C6.1, U1.17 (VDRV)
unnamed: C7.1, R1.1, U1.20 (VPWR)
unnamed: C22.2, U3.6 (VDD)
unnamed: C23.1, U3.28 (~DTR)
unnamed: R7.2, U4.2 (PC13-TAMPER-RTC)
unnamed: C26.2, R15.1, U4.5 (PD0-OSC_IN), Y2.1
unnamed: C27.1, R15.2, U4.6 (PD0-OSC_OUT), Y2.2
rst: C23.2, C24.1, R13.2, SW2.1, U4.7 (NRST)
uC_RX: R12.2, TP3.1, U3.26 (TXD), U4.31 (PA10)
uC_TX: R10.2, TP4.1, U3.25 (RXD), U4.30 (PA9)

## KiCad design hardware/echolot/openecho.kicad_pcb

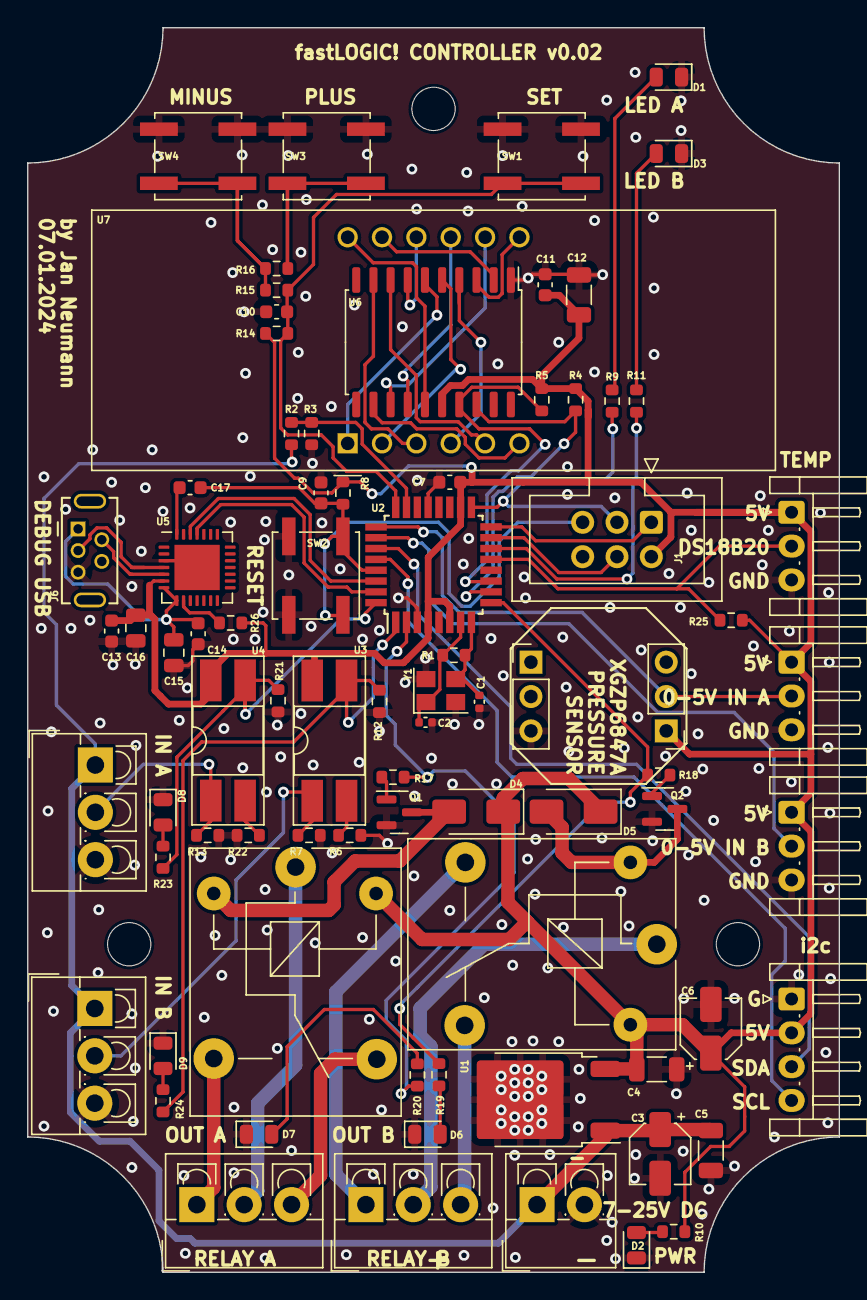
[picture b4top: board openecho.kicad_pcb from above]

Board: 2 copper layers, 60.0 x 92.0 mm, 83 parts (0 on the bottom side), 65 nets.

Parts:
C1, C2: C18pF; C_0402_1005Metric
C3, C6: C_330nF; CP_Elec_4x5.4
C4, C5: C100nF; C_1206_3216Metric
C7, C9, C10, C11, C13, C14, C17: C100nF; C_0603_1608Metric
C12: C100uF; C_1206_3216Metric
C15, C16: C10uF; C_0805_2012Metric
D1: LED_A; LED_0805_2012Metric
D2: LED_PWR; LED_0805_2012Metric
D3: LED_B; LED_0805_2012Metric
D4, D5: D; D_SMA
D6, D8, D9: LED_OUT_B; LED_0805_2012Metric
D7: LED_OUT_A; LED_0805_2012Metric
H1, H3, H5: MH; MountingHole_3.2mm_M3_DIN965
J1: AVR-ISP-6; IDC-Header_2x03_P2.54mm_Vertical
J3: DS18B20; JST_EH_S3B-EH_1x03_P2.50mm_Horizontal
J4: 12-24V; TerminalBlock_4Ucon_1x02_P3.50mm_Vertical
J5: I2C; JST_EH_S4B-EH_1x04_P2.50mm_Horizontal
J6: USB_B_Mini; USB_Mini-B_Tensility_54-00023_Vertical
J8: 12-24V_IN_A; TerminalBlock_4Ucon_1x03_P3.50mm_Vertical
J9: 12-24V_IN_B; TerminalBlock_4Ucon_1x03_P3.50mm_Vertical
J10: 0-5V_ANALOG_IN_A; JST_EH_S3B-EH_1x03_P2.50mm_Horizontal
J11: PRES_SENS_BOTTOM; PinHeader_1x03_P2.54mm_Vertical
J12: PRES_SENS_TOP; PinHeader_1x03_P2.54mm_Vertical
J13: 0-5V_ANALOG_IN_B; JST_EH_S3B-EH_1x03_P2.50mm_Horizontal
J14: RELAY_OUT_B; TerminalBlock_4Ucon_1x03_P3.50mm_Vertical
J15: RELAY_OUT_A; TerminalBlock_4Ucon_1x03_P3.50mm_Vertical
K1, K2: SANYOU_SRD_Form_C; Relay_SPDT_SANYOU_SRD_Series_Form_C
Q1, Q2: MMBT5551L; SOT-23
R1: R1M; R_0603_1608Metric
R2, R4, R5, R7, R8, R12, R13, R14, R21: R10k; R_0603_1608Metric
R3, R17, R18: R2.2k; R_0603_1608Metric
R6, R22: R470; R_0603_1608Metric
R9, R10, R11, R15, R19, R20, R23, R24: R330; R_0603_1608Metric
R16: R620; R_0603_1608Metric
R25, R26: R4.7k; R_0603_1608Metric
SW1: SET; SW_Push_1P1T_NO_CK_KSC7xxJ
SW2: reset; SW_Push_1P1T_NO_CK_KSC7xxJ
SW3: PLUS; SW_Push_1P1T_NO_CK_KSC7xxJ
SW4: MINUS; SW_Push_1P1T_NO_CK_KSC7xxJ
U1: LM78M05_TO252; TO-252-2
U2: ATmega328P-A; TQFP-32_7x7mm_P0.8mm
U3, U4: EL817; DIP-4_W8.89mm_SMDSocket_LongPads
U5: CP2102N-Axx-xQFN28; QFN-28-1EP_5x5mm_P0.5mm_EP3.35x3.35mm
U6: TM1637; SOP-20_7.5x12.8mm_P1.27mm
U7: CA56-12SRWA
Y1: Crystal_25MHz; Crystal_SMD_3225-4Pin_3.2x2.5mm

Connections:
0-5V_IN_A: J10.2, J12.2, U2.25 (PC2)
0-5V_IN_B: J13.2, U2.26 (PC3)
+5V: C4.1, C6.1, C7.1, C11.1, C12.1, C13.1, C16.1, D4.1 (K), D5.1 (K), J1.2 (VCC), J3.1, J5.2, J10.1, J12.1, J13.1, K1.5, K2.5, R4.1, R5.1, R8.1, R10.2, R14.1, R25.1, R26.1, U1.3 (VO), U2.4 (VCC), U2.6 (VCC), U2.18 (AVCC), U3.4, U4.4, U5.6 (VDD), U6.16 (VDD)
+12V: C3.1, C5.1, J4.1, J8.1, J9.1, R2.1, U1.1 (VI)
BUTTON: C10.1, R14.2, R15.2, SW1.2, U2.24 (PC1)
DIG_IN_A: R21.1, R23.2, U2.32 (PD2), U4.3
DIG_IN_B: R12.1, R24.2, U2.1 (PD3), U3.3
DS18B20_DATA: J3.2, R25.2, U2.13 (PB1)
D_OUT_A: R17.1, R20.2, U2.2 (PD4)
D_OUT_B: R18.1, R19.2, U2.9 (PD5)
GND: C1.1, C2.2, C3.2, C4.2, C5.2, C6.2, C7.2, C9.2, C10.2, C11.2, C12.2, C13.2, C14.1, C15.1, C16.2, D1.1 (K), D2.1 (K), D3.1 (K), D6.1 (K), D7.1 (K), D8.1 (K), D9.1 (K), J1.6 (GND), J3.3, J4.2, J5.1, J6.5 (GND), J8.3, J9.3, J10.3, J11.3, J13.3, Q1.2 (E), Q2.2 (E), R3.2, R6.2, R7.2, R12.2, R13.2, R21.2, R22.2, SW1.1, SW2.1, SW3.1, SW4.1, U1.2 (GND), U2.3 (GND), U2.5 (GND), U2.21 (GND), U5.3 (GND), U5.29 (GND), U6.1 (GND), Y1.2, Y1.4
LED_A: J1.3 (SCK), R9.2, U2.17 (PB5)
LED_B: R11.2, U2.14 (PB2)
MISO: J1.1 (MISO), U2.16 (PB4)
MOSI: J1.4 (MOSI), U2.15 (PB3)
unnamed: D1.2 (A), R9.1
unnamed: D2.2 (A), R10.1
unnamed: D3.2 (A), R11.1
unnamed: D4.2 (A), K1.2, Q1.3 (C)
unnamed: D5.2 (A), K2.2, Q2.3 (C)
unnamed: D6.2 (A), R19.1
unnamed: D7.2 (A), R20.1
unnamed: D8.2 (A), R23.1
unnamed: D9.2 (A), R24.1
unnamed: J6.3 (D+), U5.4 (D+)
unnamed: J6.2 (D-), U5.5 (D-)
unnamed: C14.2, C15.2, J6.1 (VBUS), U5.7 (VREGIN), U5.8 (VBUS)
unnamed: J8.2, R13.1, U4.1
unnamed: J9.2, R7.1, U3.1
unnamed: J14.1, K2.3
unnamed: J14.2, K2.1
unnamed: J14.3, K2.4
unnamed: J15.1, K1.3
unnamed: J15.2, K1.1
unnamed: J15.3, K1.4
unnamed: Q1.1 (B), R17.2
unnamed: Q2.1 (B), R18.2
unnamed: R6.1, U3.2
unnamed: R15.1, R16.2, SW4.2
unnamed: R16.1, SW3.2
unnamed: R22.1, U4.2
unnamed: R4.2, U2.10 (PD6), U6.18 (CLK)
unnamed: R5.2, U2.11 (PD7), U6.17 (DIO)
unnamed: C2.1, R1.2, U2.7 (XTAL1/PB6), Y1.1
unnamed: C1.2, R1.1, U2.8 (XTAL2/PB7), Y1.3
unnamed: C17.1, U5.28 (~DTR)
unnamed: R26.2, U5.9 (~RST)
unnamed: U6.15 (GRID1), U7.12 (CA1)
unnamed: U6.14 (GRID2), U7.9 (CA2)
unnamed: U6.13 (GRID3), U7.8 (CA3)
unnamed: U6.12 (GRID4), U7.6 (CA4)
unnamed: U6.2 (SEG1/KS1), U7.11 (a)
unnamed: U6.3 (SEG2/KS2), U7.7 (b)
unnamed: U6.4 (SEG3/KS3), U7.4 (c)
unnamed: U6.5 (SEG4/KS4), U7.2 (d)
unnamed: U6.6 (SEG5/KS5), U7.1 (e)
unnamed: U6.7 (SEG6/KS6), U7.10 (f)
unnamed: U6.8 (SEG7/KS7), U7.5 (g)
unnamed: U6.9 (SEG8/KS8), U7.3 (DPX)
RX: U2.30 (PD0), U5.26 (TXD)
SCL: J5.4, U2.28 (PC5)
SDA: J5.3, U2.27 (PC4)
TX: U2.31 (PD1), U5.25 (RXD)
reset: C9.1, C17.2, J1.5 (~RST), R8.2, SW2.2, U2.29 (~RESET/PC6)
v_sens: R2.2, R3.1, U2.23 (PC0)
